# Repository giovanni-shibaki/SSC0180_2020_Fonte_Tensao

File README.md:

# SSC0180_2020_Fonte_Tensao
Projeto de estudo e desenvolvimento de uma fonte elétrica na matéria de SSC0180 USP 2020. Vamos partir da tensão da tomada (220V ou 127V) e teremos que transforma-la de 127V/220V Corrente Alternada em uma tensão adequada para alimentar nosso circuito. Isto é, de 3V-12V em Corrente Contínua.

## Diagrama da Fonte
### No Falstad

### Critérios
* Tensão ajustável entre 3V e 12V 
* Corrente de 100mA
* Baixo Custo

### Componentes e seus Valores
| Componente        | Especificações      | Valor (Unidade)|
| :---              |     :---:           |          :---  |
| Resistor          | 120Ω                | [R$0,86](https://tinyurl.com/y8pryj5b)         |
| Resistor          | 390Ω                | [R$0,30](https://produto.mercadolivre.com.br/MLB-1008875897-kit-100un-resistores-2w-de-potncia-escolha-1-valor-ohmico-_JM?quantity=1&variation=24614777985#reco_item_pos=0&reco_backend=machinalis-seller-items-pdp&reco_backend_type=low_level&reco_client=vip-seller_items-above&reco_id=10f4f528-f90c-4ae4-a79b-d7bc075436cd)         |
| Resistor          | 1kΩ                 | [R$0,13](https://produto.mercadolivre.com.br/MLB-1399314776-resistor-1k-ohms-100-unidades-_JM?quantity=1#position=1&type=item&tracking_id=52f519e5-730a-499f-b8c5-b95d75cb7d62)         |
| Resistor          | 2kΩ                 | [R$0,16](https://produto.mercadolivre.com.br/MLB-1359755617-100un-resistor-18w-2k-2000-ohms-_JM?quantity=1#position=1&type=item&tracking_id=cfe0aced-991b-46f7-ad48-868c569c5428)         |
| Potenciômetro     | 5kΩ                 | [R$1,09](https://www.baudaeletronica.com.br/potenciometro-linear-de-5k-5000.html)         |
| Capacitor         | 470μF               | [R$1,70](https://produto.mercadolivre.com.br/MLB-845022301-10x-capacitor-eletrolitico-470uf-x-25v-470-uf-470uf-b-_JM?matt_tool=79246729&matt_word&gclid=CjwKCAjw_LL2BRAkEiwAv2Y3Sb3K7a3Tunb33Op9IqjhFXaI9mM8M3F670_AOoe76uXUgjvsgv6zNBoC-swQAvD_BwE&quantity=1)         |
| Transistor        | 15V  e 500mA        | [R$1,12](https://produto.mercadolivre.com.br/MLB-939476869-10x-transistor-2sa1015-a1015-_JM?quantity=1&shippingOptionId=undefined)         |
| Diodo de Zener    | 0,5W                | [R$0,21](https://produto.mercadolivre.com.br/MLB-1395521239-diodo-zener-13v-05w-1n5243-lote-de-100-pecas-_JM?quantity=1#position=1&type=item&tracking_id=d4d209e7-f5b5-459a-9025-ddfa3d9fc5e1)         |
| Ponte Retificadora| 1000V e 2A          | [R$1,96](https://produto.mercadolivre.com.br/MLB-1151520283-ponte-retificadora-2w10-2a-1000v-lote-com-10-pecas-_JM?quantity=1#position=25&type=item&tracking_id=595601ca-7ab7-4d81-a34e-d3e6fc7ebbfb)         |
| Transformador     | 15V e 500mA         | [R$25,90](https://www.filipeflop.com/produto/transformador-trafo-15v-500ma-bivolt/)         |
|LED                | Difuso 3mm          | [R$0,20](https://www.eletrogate.com/led-difuso-3mm-vermelho)    |
|Switch             | 250V e 3A           | [R$8,00](https://tinyurl.com/y9v33gzg)    |
| **Custo Total**   |                     | **R$41,63**        |          
<!-- | Fios (jumper)     | 15V e 500mA         | R$            | -->
<!-- | Protoboard        | 830 Pontos          | R$            | -->
### Justificativa dos Componentes Escolhidos
1. Resistores
    * R1 (390Ω) : Limita corrente eletrica que passa pelo Zener  
    * R2 (5kΩ)  : Potenciômetro , regula a corrente de base que vai para o transistor, assim a fonte varia de 12v e 100mA para 3v e ~24mA
    * R3 (2kΩ)  : Como está ligado em série com o potênciometro ele também serve para regular a tensão de base que vai para o transistor e consequentemente a voltagem de saída de nossa fonte.
    * R4 (120Ω) : Auxiliar para a regulagem da tensão de saída (é como a saída da fonte). Representa a saída da Fonte no pior caso (120ohms)
    * R5 (1kΩ)  : Deixa a corrente adequada para o funcionamento do LED
2. Capacitor
    * Serve para estabilizar a tensão do circuito
    * Nosso circuito chega em um pico de 15V, então o de 25V é mais do que suficiente.
3. Transistor
    * Atenua a corrente e a tensão que vai para a saída do sistema através da corrente de base de 1mA que passa pelo potenciometro R2 e a resistência R3.
4.  Diodo de Zener
    * Equivale a : 13V e 20mA. Isso pois (P=i*U) P = 13V * 0,02A = 0.26W, então um diodo de 0,5W é mais do que suficiente
    * É importante ressaltar que: a corrente que passa pelo diodo é a corrente que atravessa o resistor 390 Ohm (R1: 6mA ) menos 3mA que vai pro transistor ==> 3mA passando no Zener
    * Como opera inversamente, ele mantem o valor da tensão máxima, no caso os 13V.
5. Ponte Retificadora
    * Transforma AC em DC que sai de nosso transformador
6. Transformador
    * 127V ou 220V através de chave seletora no circuito. Potência de 7,5W
7. LED
    * Indica que o circuito está ligada, algo trivial
<!-- 8. GND
    - O ground faz o escape da energia para um local seguro, por precaução -->
<!-- 8. Fios
    - Conectam os componentes do circuito  -->
<!-- 9. Protoboard
    - Base de construção de circuitos. Escolhida por praticidade, não necessita soldar para conectar componentes do circuito -->

## Circuito no Falstad
* http://tinyurl.com/ycns7so6

## Projeto do Esquemático e do PCB no EAGLE
### Esquemático
O projeto esquemático é análogo a uma "planta" de um circuito. Nele são ilustrados os componentes, valores e suas conexões no circuito.<br>

### PBC ( _Printed Circuit Board_ )
O PCB é uma placa dedicada a expressar as conexões de um determinado circuito. Permitem uma instalação precisa, compacta e confiável dos componentes. <br>
<br>
OBS: os arquivos pertinentes ao projeto realizado no EAGLE podem ser encontrados neste mesmo repositório, na pasta "eagle"

## Fotos do Circuito (EM BREVE)
` incluir fotos da placa/protoboard`

## Vídeo Explicativo

## Participantes

* **Giovanni Shibaki Camargo** - [giovanni-shibaki](https://github.com/giovanni-shibaki)

* **Melissa Motoki Nogueira**  - [mmotokki](https://github.com/mmotokki)

* **Pedro Kenzo Muramatsu Carmo** - [Muramatsu2602](https://github.com/Muramatsu2602)

## Agradecimentos

* Agradecimentos ao [Prof Simões](https://github.com/simoesusp) pela oportunidade de realizar o projeto.
* Agradecimentos à equipe pela dedicação e afinco nestes tempos anômalos
* Special thanks to [Mehdi Sadaghdar](https://www.youtube.com/watch?v=j4u8fl31sgQ&list=PLr_CZLgMkHeXc_45uIgYutY0m6fqmI5du), whose insighful videos made learning electronics more enjoyable!

## Observações

* O circuito montado no Falstad e no Eagle são baseados em um transformador de 127V. Caso 220V fosse utilizado algumas possíveis mudanças poderiam ser necessarias, podendo ser utilizado um Capacitor de 1000uF.
* O embasamento teórico para a elaboração da fonte pode ser encontrada no [livro](https://www.amazon.com.br/Eletr%C3%B4nica-B%C3%A1sica-Computa%C3%A7%C3%A3o-Annibal-Junior/dp/8521616996) base da disciplina
* A organização do projeto, bem como reuniões e discussões, pode ser conferida neste [doc](https://docs.google.com/document/d/1Gu77hdx1NdPrP7V1o1ucyJgEMdmdFqv-v6fdKn2zFD0/edit?usp=sharing)

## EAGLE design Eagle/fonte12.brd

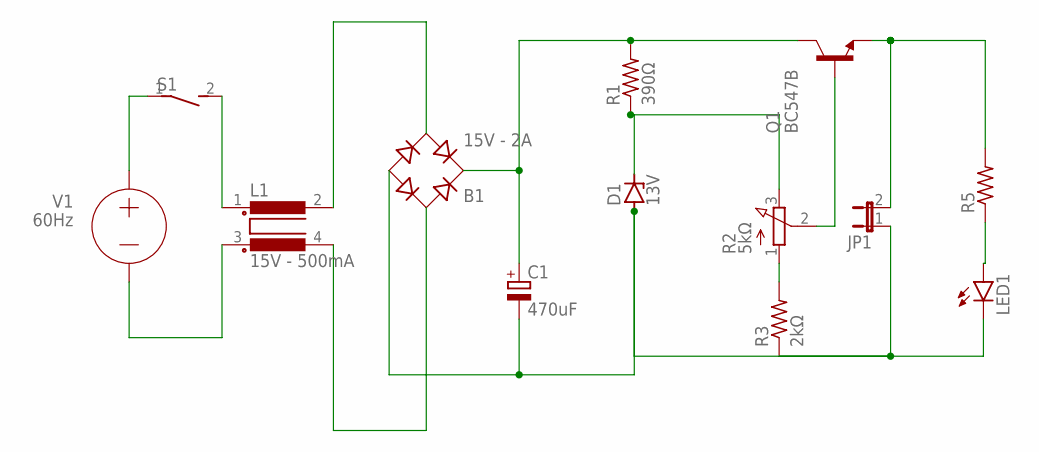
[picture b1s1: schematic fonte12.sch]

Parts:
B1: 15V - 2A; RB1A
C1: 470uF; E3,5-10
D1: 13V; DO41Z10
JP1: JP1E; JP1
L1: 15V - 500mA; B2
LED1: LED5MM
Q1: BC547B; TO92
R1: 390Ω; 0309/12
R2: 5kΩ; 3RP/1610N
R3: 2kΩ; 0309/12
R5: R-US_0309/12; 0309/12
S1: DS01E; DS-01

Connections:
unnamed: R2.1 (A), R3.2
unnamed: JP1.2, Q1.1 (E), R5.2
unnamed: B1.AC2, L1.2
unnamed: B1.AC1, L1.4
unnamed: B1.+, C1.+, Q1.3 (C), R1.2
unnamed: B1.-, C1.-, D1.A, JP1.1, LED1.K (C)
unnamed: D1.C, R1.1, R2.3 (E)
unnamed: LED1.A, R5.1
unnamed: L1.1, S1.2
unnamed: Q1.2 (B), R2.2 (S)

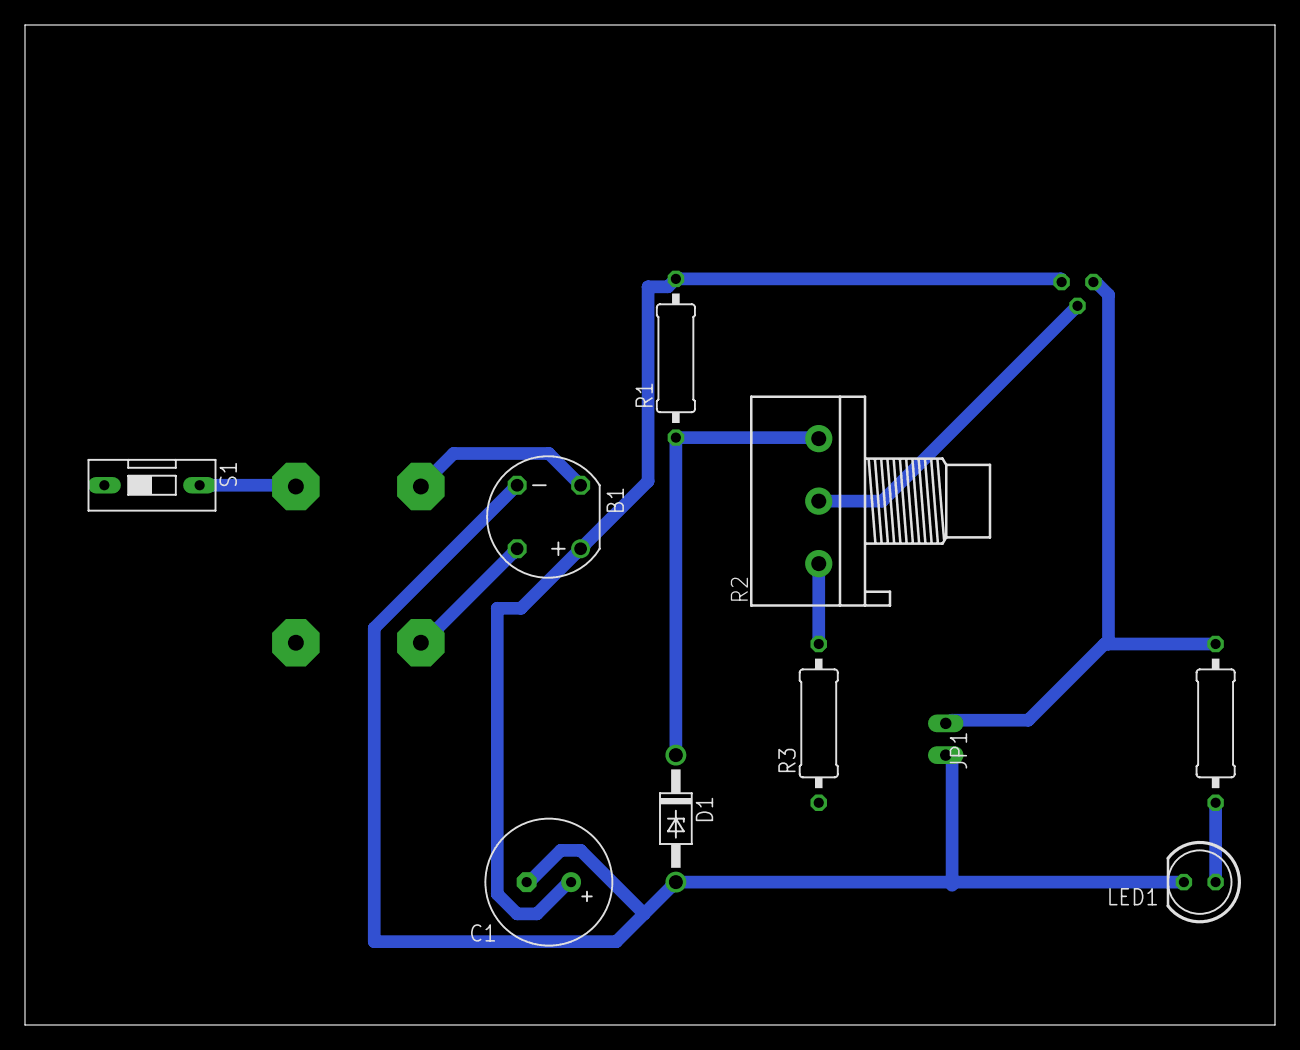
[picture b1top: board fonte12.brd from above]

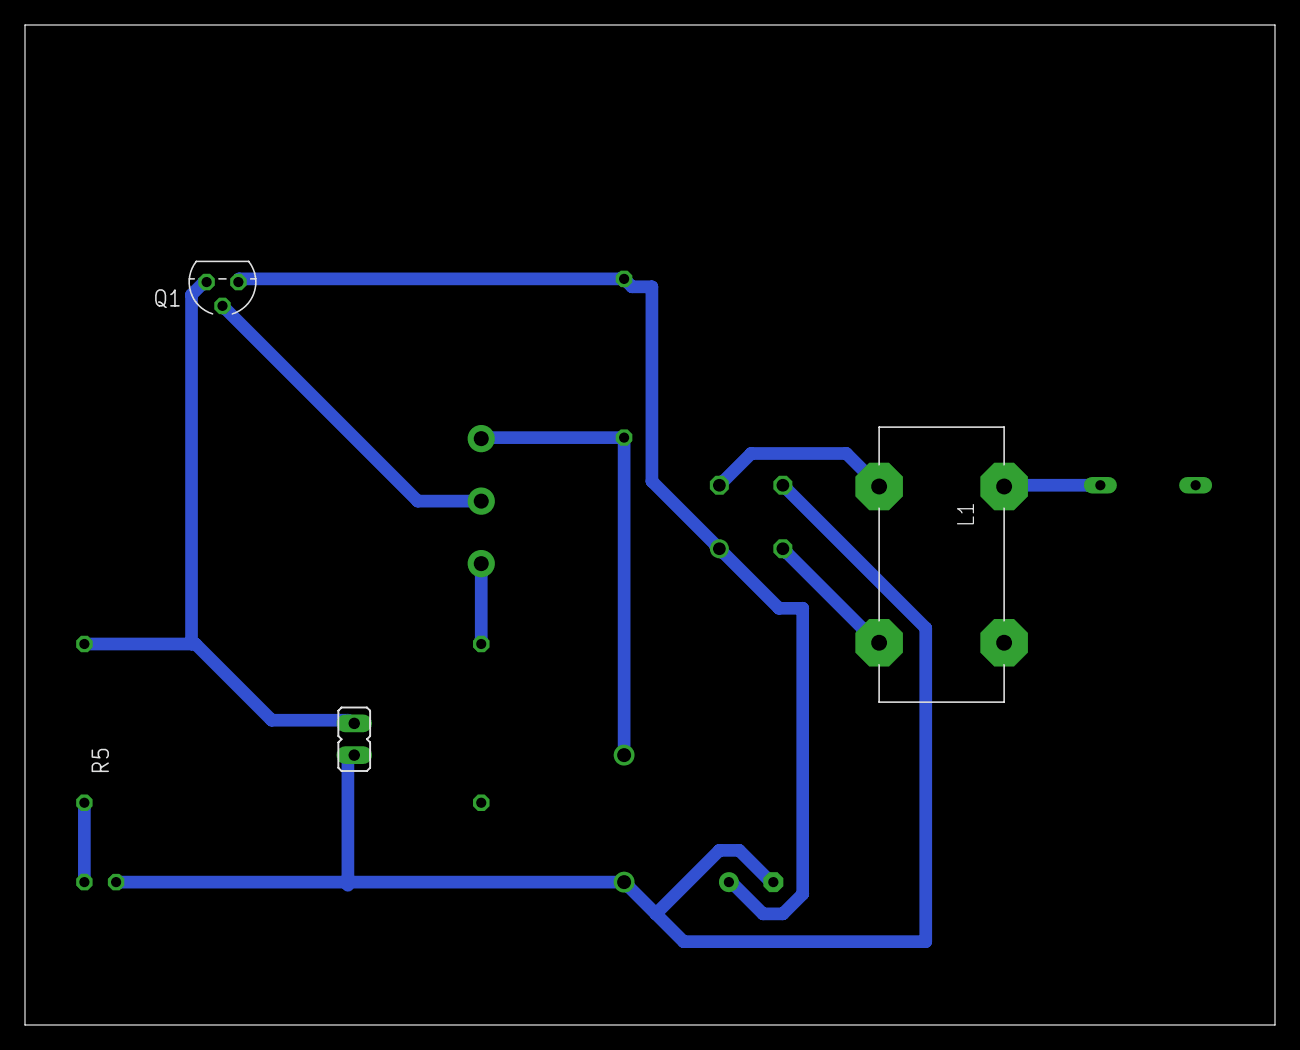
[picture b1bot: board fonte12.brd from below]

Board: 2 copper layers, 100.0 x 80.0 mm, 12 parts (3 on the bottom side), 10 nets.

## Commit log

2020-05-19 Genesis
    Mudei o README pra ficar mais show
2020-05-19 Grammar Check
2020-05-19 Minor Changes in identation
2020-05-26 Minor changes in README
2020-06-02 tabela moReadMe
2020-06-02 Little
2020-06-02 Justificativas
2020-06-02 README atualizado
2020-06-09 New README
2020-06-09 READ.ME
2020-06-09 README
2020-06-09 Falstad
2020-06-09 Thanks to...
2020-06-10 quick change
2020-06-10 prof simoes github
2020-06-16 PBC images and new README
2020-06-16 Arquivos EAGLE
    Upload dos arquivos (sch, brd, epf e afins) do projeto do Eagle.
2020-06-16 readMe again
2020-06-16 Novas imagens
    Troquei o modelo do potenciômetro, para ficar mais semelhante ao do prof.
2020-06-16 Atualização
    Atualizei os arquivos do circuito, uma vez que precisei trocar o modelo do potenciômetro.
2020-06-16 PDF de impressão
    Arrumei, selecionando a opção 'mirror'
2020-06-19 VIDEO
2020-06-19 video image
2020-06-19 new url
2020-06-30 R4 e Livro
2020-06-30 Diagrama no Falstad com observação para R4
2020-06-30 Ajuste - adicionei a saida
    Conforme observado pelo prof.
2020-06-30 Ajustes pós-apresentação
    Adicionou-se a saída do sistema no lugar do R4
